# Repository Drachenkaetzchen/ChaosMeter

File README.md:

The ChaosMeter. Further details will be announced at 31C3.

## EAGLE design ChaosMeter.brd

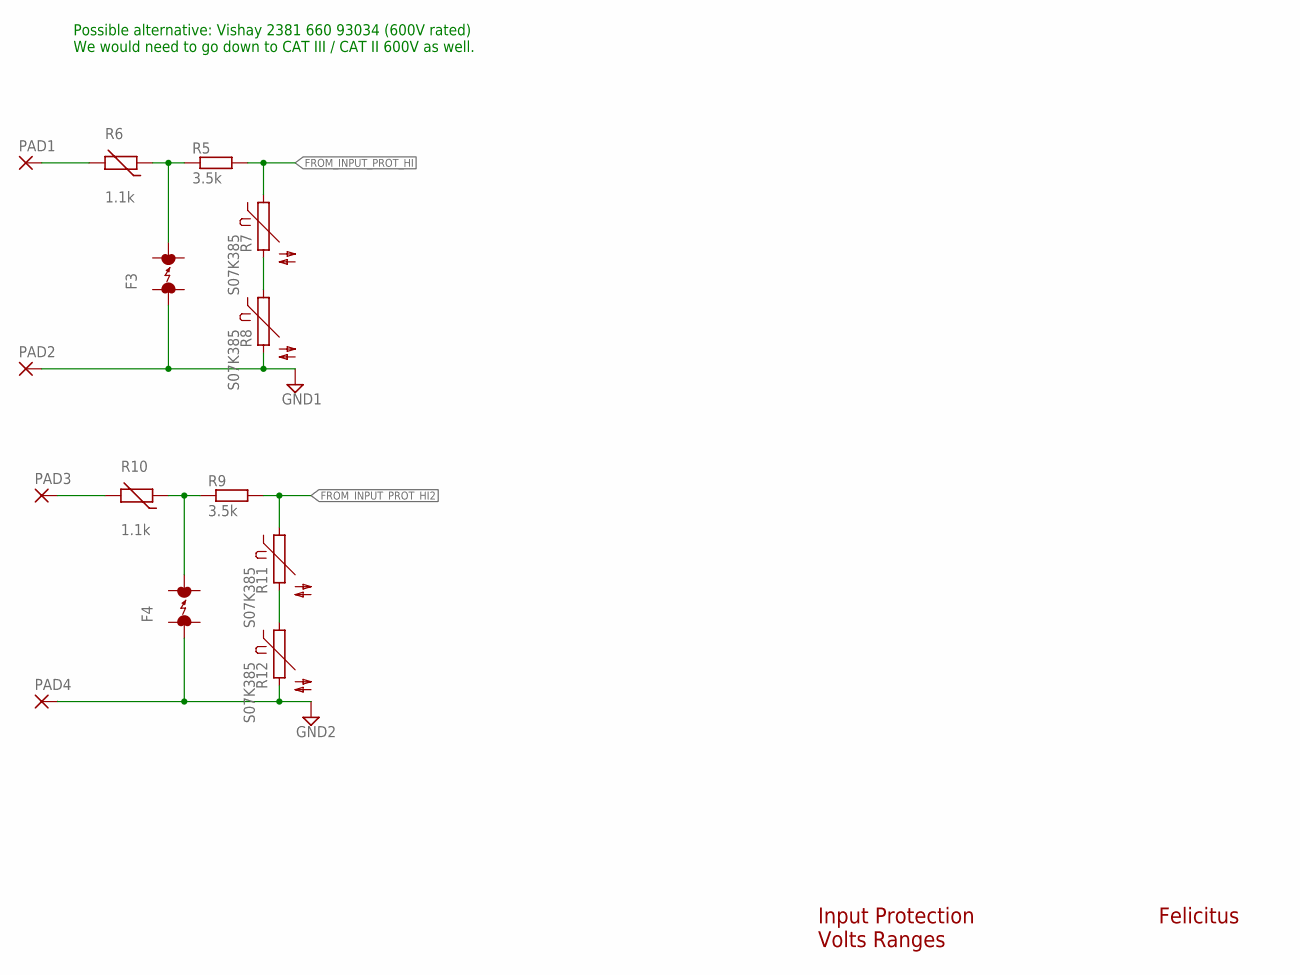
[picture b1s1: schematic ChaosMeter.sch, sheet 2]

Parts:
F3, F4: ARRESTER; EPCOS_N81
PAD1, PAD2, PAD3, PAD4: 2,54/1,1
R5, R9: 3.5k; P0613/15
R6, R10: 1.1k; R-5
R7, R8, R11, R12: S07K385

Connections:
FROM_INPUT_PROT_HI: R5.2, R7.1; also elsewhere on the board
FROM_INPUT_PROT_HI2: R9.2, R11.1; also elsewhere on the board
GND1: F3.1, PAD2.1, R8.2; also elsewhere on the board
GND2: F4.1, PAD4.1, R12.2; also elsewhere on the board
INPUT_JACK_HI: PAD1.1, R6.2
INPUT_JACK_HI1: PAD3.1, R10.2
unnamed: F3.2, R5.1, R6.1
unnamed: R11.2, R12.1
unnamed: R7.2, R8.1
unnamed: F4.2, R9.1, R10.1

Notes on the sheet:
Possible alternative: Vishay 2381 660 93034 (600V rated) We would need to go down to CAT III / CAT II 600V as well.
Input Protection Volts Ranges
Felicitus

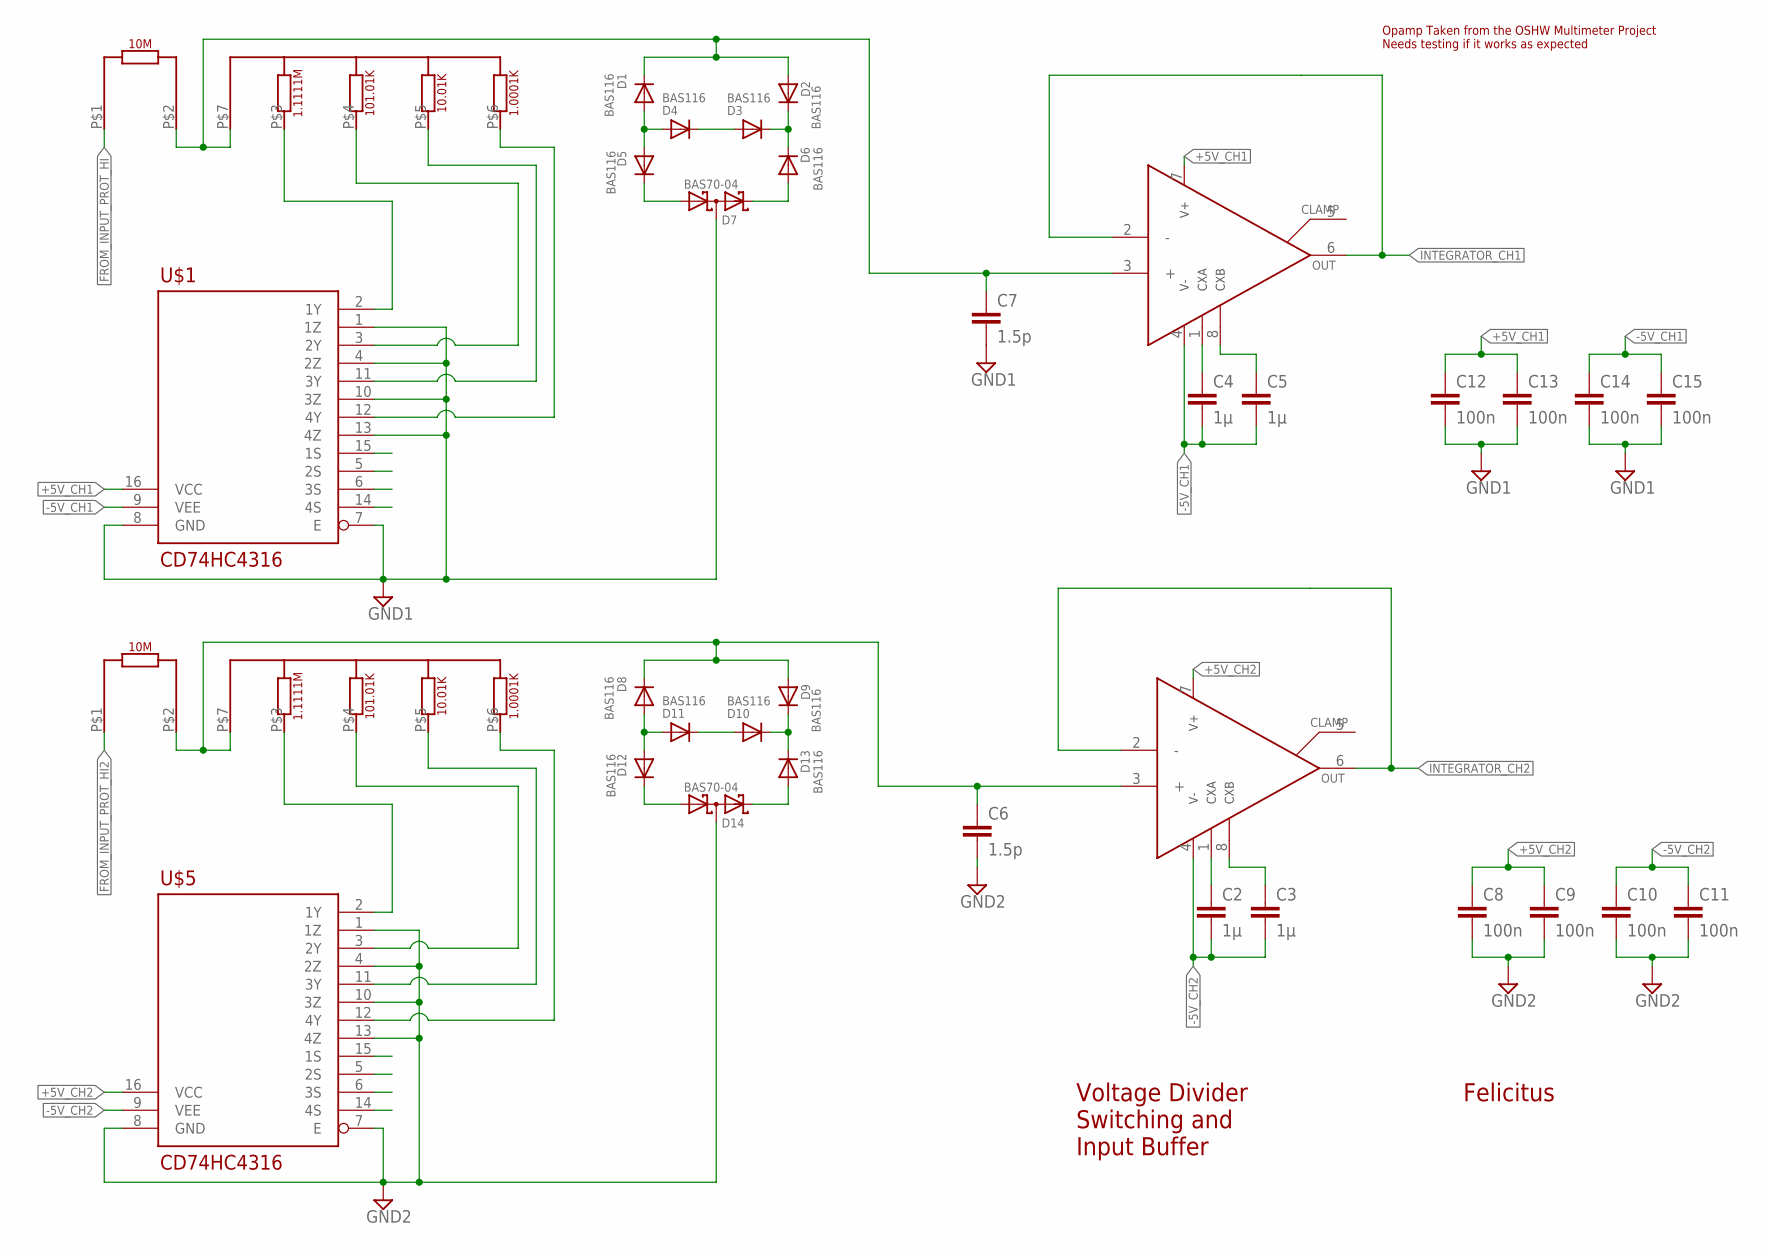
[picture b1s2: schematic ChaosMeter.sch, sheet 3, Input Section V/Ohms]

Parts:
C2, C3, C4, C5: 1µ; C0603
C6, C7: 1.5p; C0603
C8, C9, C10, C11, C12, C13, C14, C15: 100n; C0603
D1, D2, D3, D4, D5, D6, D8, D9, D10, D11, D12, D13: BAS116; SOT23-3
D7, D14: BAS70-04; SOT23
U$1, U$5: CD74HC4316; SOP65P640X110-16N
U$3, U$4: CADDOCK-1776-C4815
U$6, U$7: TLC2654A; SOIC8

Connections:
+5V_CH1: C12.1, C13.1, U$1.16 (VCC), U$7.7 (V+)
+5V_CH2: C8.1, C9.1, U$5.16 (VCC), U$6.7 (V+)
-5V_CH1: C4.2, C5.2, C14.1, C15.1, U$1.9 (VEE), U$7.4 (V-)
-5V_CH2: C2.2, C3.2, C10.1, C11.1, U$5.9 (VEE), U$6.4 (V-)
FROM_INPUT_PROT_HI: U$3.P$1; also elsewhere on the board
FROM_INPUT_PROT_HI2: U$4.P$1; also elsewhere on the board
GND1: C7.2, C12.2, C13.2, C14.2, C15.2, D7.3 (C1A2), U$1.1 (1Z), U$1.4 (2Z), U$1.7 (E), U$1.8 (GND), U$1.10 (3Z), U$1.13 (4Z); also elsewhere on the board
GND2: C6.2, C8.2, C9.2, C10.2, C11.2, D14.3 (C1A2), U$5.1 (1Z), U$5.4 (2Z), U$5.7 (E), U$5.8 (GND), U$5.10 (3Z), U$5.13 (4Z); also elsewhere on the board
INTEGRATOR_CH1: U$7.6 (OUT)
INTEGRATOR_CH2: U$6.6 (OUT)
unnamed: D3.1 (A), D4.3 (C)
unnamed: D2.3 (C), D3.3 (C), D6.3 (C)
unnamed: D1.1 (A), D4.1 (A), D5.1 (A)
unnamed: D5.3 (C), D7.1 (A1)
unnamed: D6.1 (A), D7.2 (C2)
unnamed: D10.1 (A), D11.3 (C)
unnamed: C7.1, D1.3 (C), D2.1 (A), U$3.P$2, U$3.P$7, U$7.3 (+)
unnamed: U$1.2 (1Y), U$3.P$3
unnamed: D9.3 (C), D10.3 (C), D13.3 (C)
unnamed: U$1.3 (2Y), U$3.P$4
unnamed: U$1.11 (3Y), U$3.P$5
unnamed: U$1.12 (4Y), U$3.P$6
unnamed: D8.1 (A), D11.1 (A), D12.1 (A)
unnamed: D12.3 (C), D14.1 (A1)
unnamed: D13.1 (A), D14.2 (C2)
unnamed: C6.1, D8.3 (C), D9.1 (A), U$4.P$2, U$4.P$7, U$6.3 (+)
unnamed: U$4.P$3, U$5.2 (1Y)
unnamed: U$4.P$4, U$5.3 (2Y)
unnamed: U$4.P$5, U$5.11 (3Y)
unnamed: U$4.P$6, U$5.12 (4Y)
unnamed: C2.1, U$6.1 (CXA)
unnamed: C3.1, U$6.8 (CXB)
unnamed: C4.1, U$7.1 (CXA)
unnamed: C5.1, U$7.8 (CXB)

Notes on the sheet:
Felicitus
Voltage Divider Switching and Input Buffer
Opamp Taken from the OSHW Multimeter Project Needs testing if it works as expected

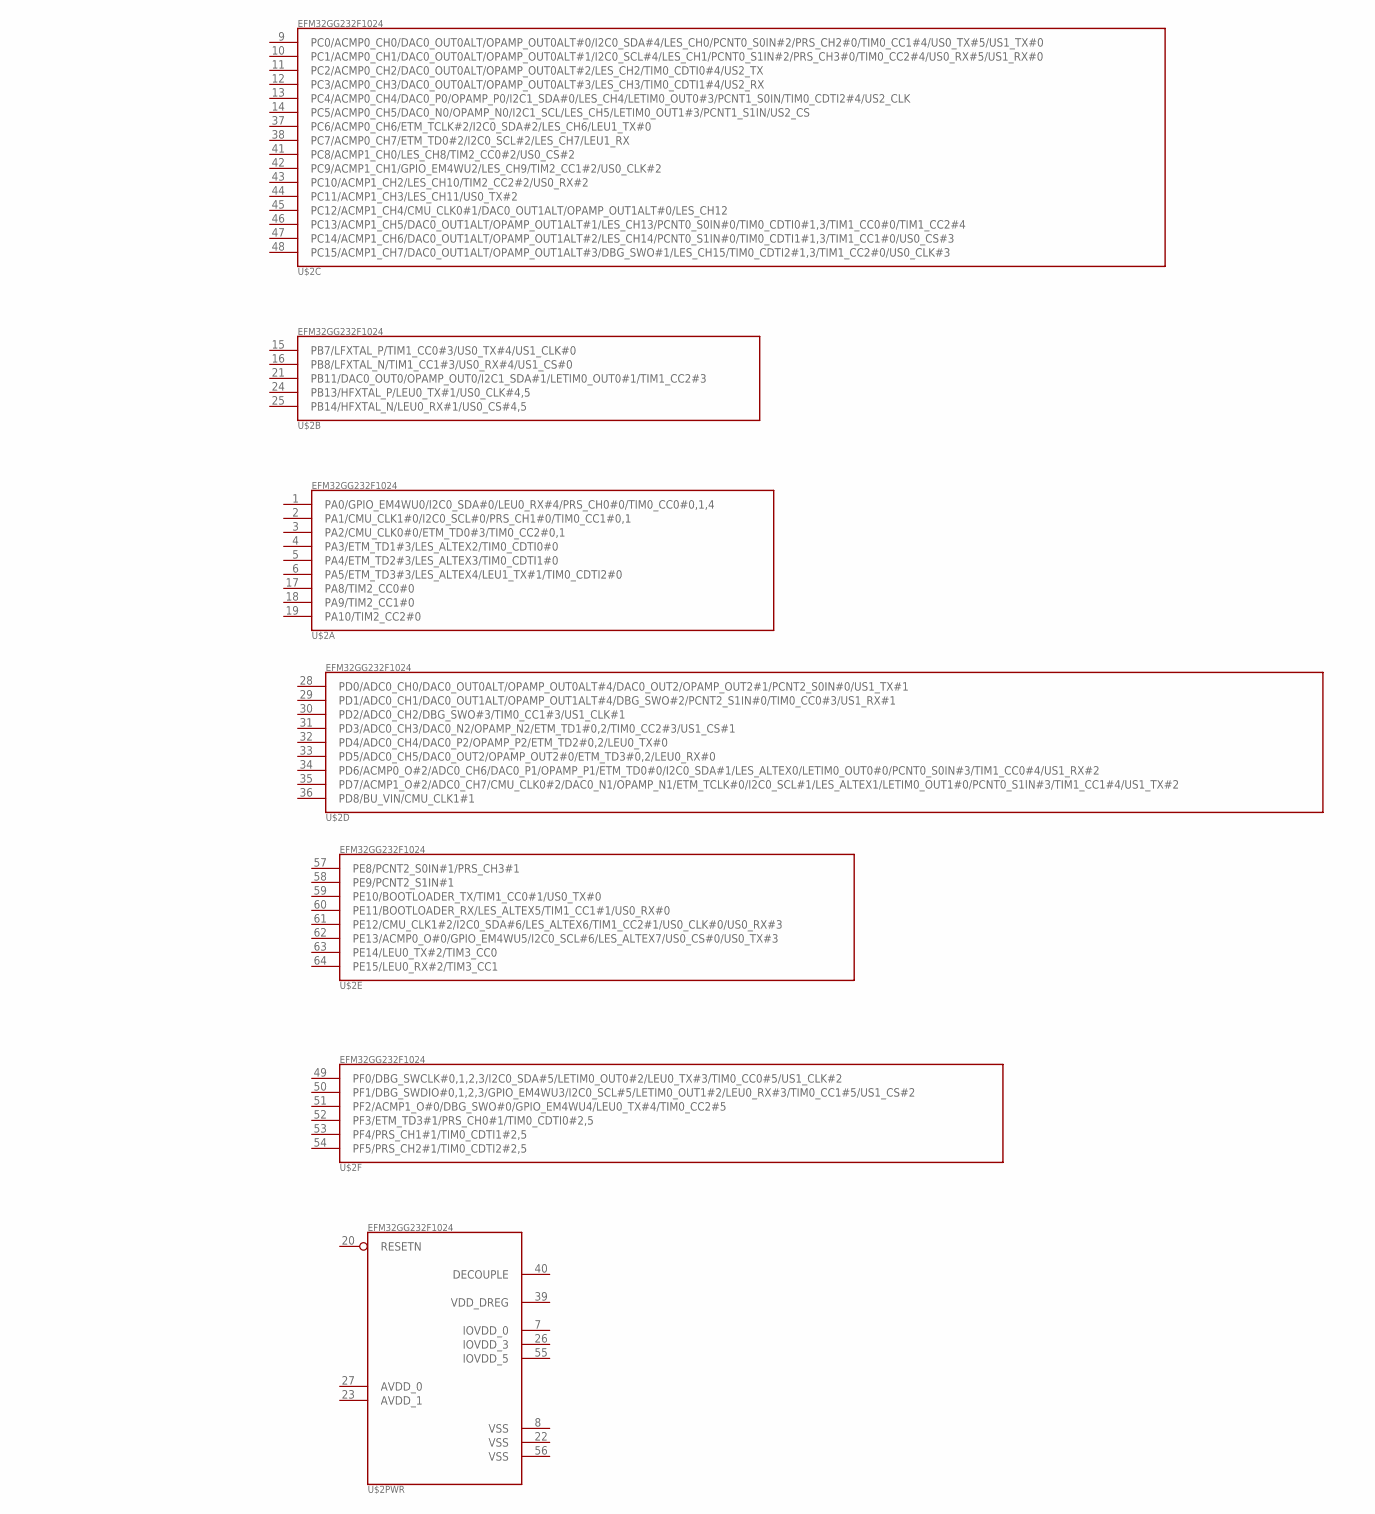
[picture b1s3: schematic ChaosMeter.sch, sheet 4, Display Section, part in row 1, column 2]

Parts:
U$2: EFM32GG232F1024; QFP64

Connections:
AVDD_0: U$2.27 (AVDD_0)
AVDD_1: U$2.23 (AVDD_1)
DECOUPLE: U$2.40 (DECOUPLE)
IOVDD_0: U$2.7 (IOVDD_0)
IOVDD_3: U$2.26 (IOVDD_3)
IOVDD_5: U$2.55 (IOVDD_5)
VDD_DREG: U$2.39 (VDD_DREG)
VSS: U$2.8 (VSS), U$2.22 (VSS), U$2.56 (VSS)

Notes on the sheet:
Buttons: Digikey CKN10309CT-ND

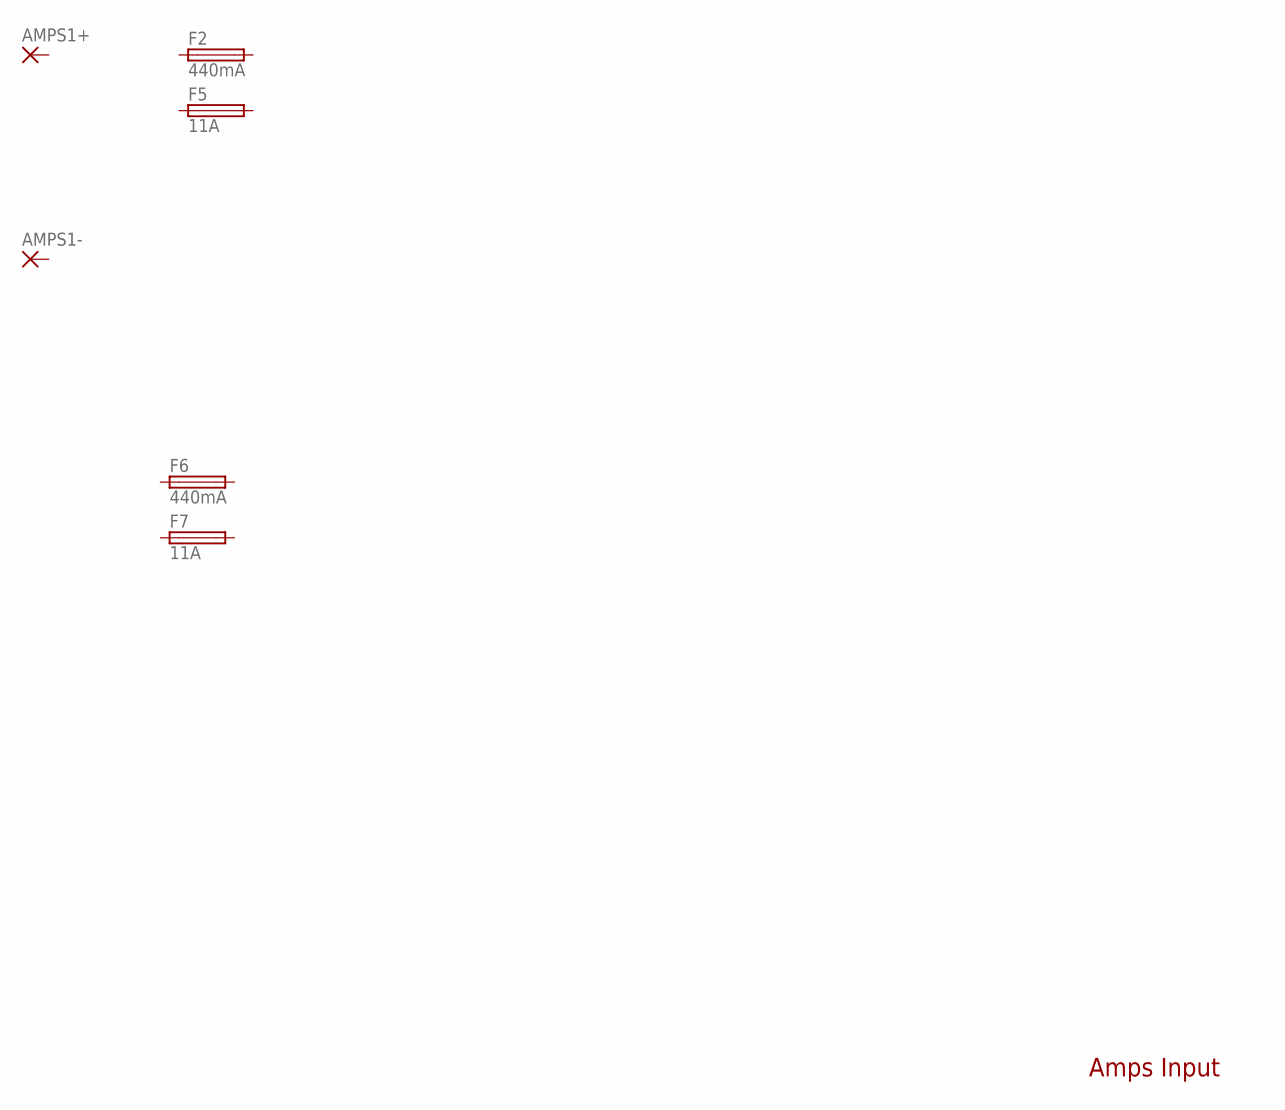
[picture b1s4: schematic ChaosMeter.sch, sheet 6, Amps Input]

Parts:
AMPS1+, AMPS1-: 2,54/1,1
F2, F6: 440mA; SH32
F5, F7: 11A; SH32

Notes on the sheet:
Amps Input

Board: 2 copper layers, 55 parts (27 on the bottom side), 39 nets, no tracks yet.

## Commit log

2014-01-03 Initial commit w/ Caddock 1776
2014-01-03 Added design note about the channel design
2014-01-07 Added Caddock 1776-C6815 and diode array
2014-01-07 Added simulation for the input resistor network
2014-02-13 Added thanks file
2014-02-13 Added initial input protection, input divider switching and buffering
2014-02-13 Added note about the buttons for the front panel
2014-02-14 Added TODO
2014-07-13 Added protection simulation for the nA range
2014-07-13 Added double fuses (11A/440mA) for the amps input

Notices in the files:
parts and their libraries:
SparkFun: Licensing: CC v3.0 Share-Alike You are welcome to use this library for commercial purposes.
EnergyMicro: CC0 License
